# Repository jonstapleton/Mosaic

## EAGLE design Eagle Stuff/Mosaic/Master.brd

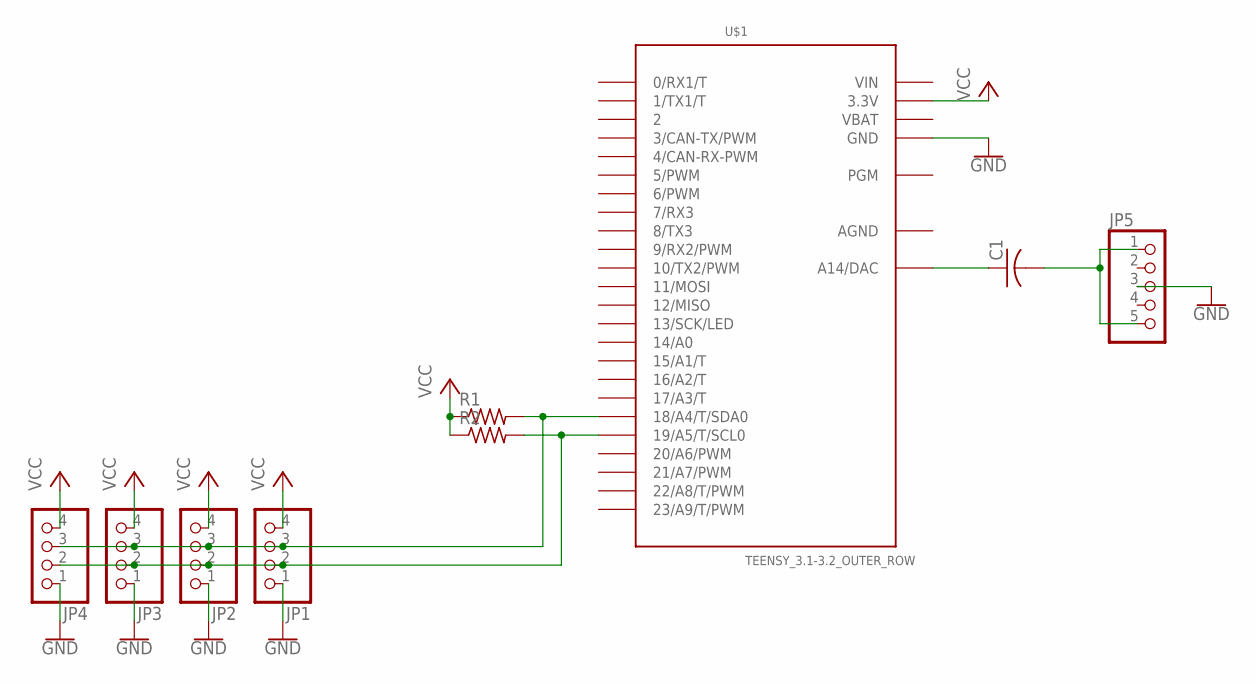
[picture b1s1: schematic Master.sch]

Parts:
C1: C-US025-030X050; C025-030X050
JP1, JP2, JP3, JP4: PINHD-1X4; 1X04
JP5: PINHD-1X5; 1X05
R1, R2: R-US_0207/7; 0207/7
U$1: TEENSY_3.1-3.2_OUTER_ROW; TEENSY_3.0-3.2&LC_OUTER_ROW

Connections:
AGND: U$1.AGND
GND: JP1.1, JP2.1, JP3.1, JP4.1, JP5.3, U$1.GND, U$1.GND1 (GND)
unnamed: JP1.3, JP2.3, JP3.3, JP4.3, R1.2, U$1.18/A4 (18/A4/T/SDA0)
unnamed: JP1.2, JP2.2, JP3.2, JP4.2, R2.2, U$1.19/A5 (19/A5/T/SCL0)
unnamed: C1.1, U$1.RESET/DAC (A14/DAC)
unnamed: C1.2, JP5.1, JP5.5
VBAT: U$1.VBAT
VCC: JP1.4, JP2.4, JP3.4, JP4.4, R1.1, R2.1, U$1.3.3V, U$1.3.3V1 (3.3V)
VIN: U$1.VIN

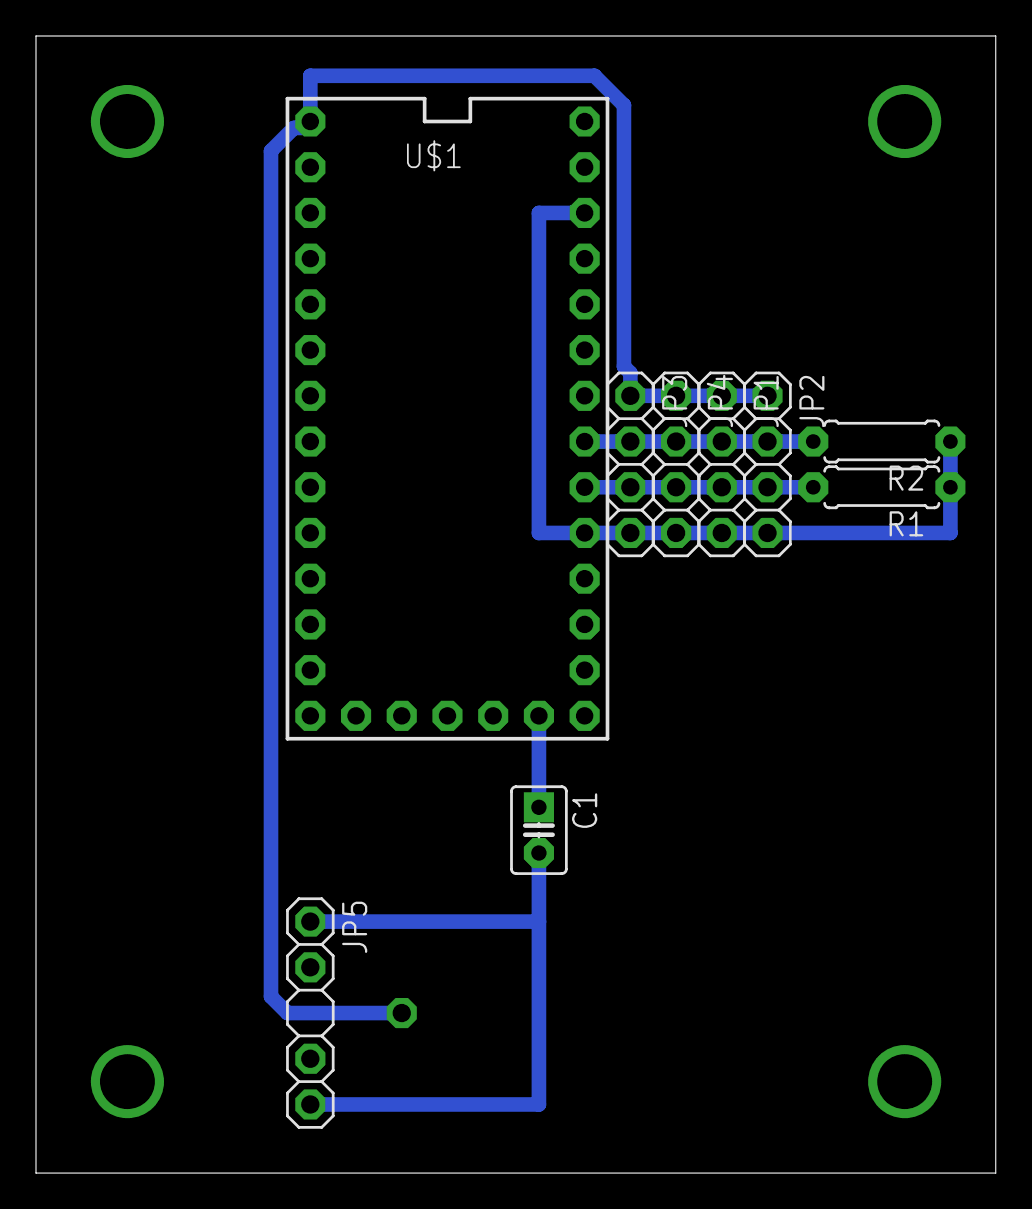
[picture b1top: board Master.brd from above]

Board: 2 copper layers, 53.3 x 63.2 mm, 9 parts (0 on the bottom side), 6 nets.

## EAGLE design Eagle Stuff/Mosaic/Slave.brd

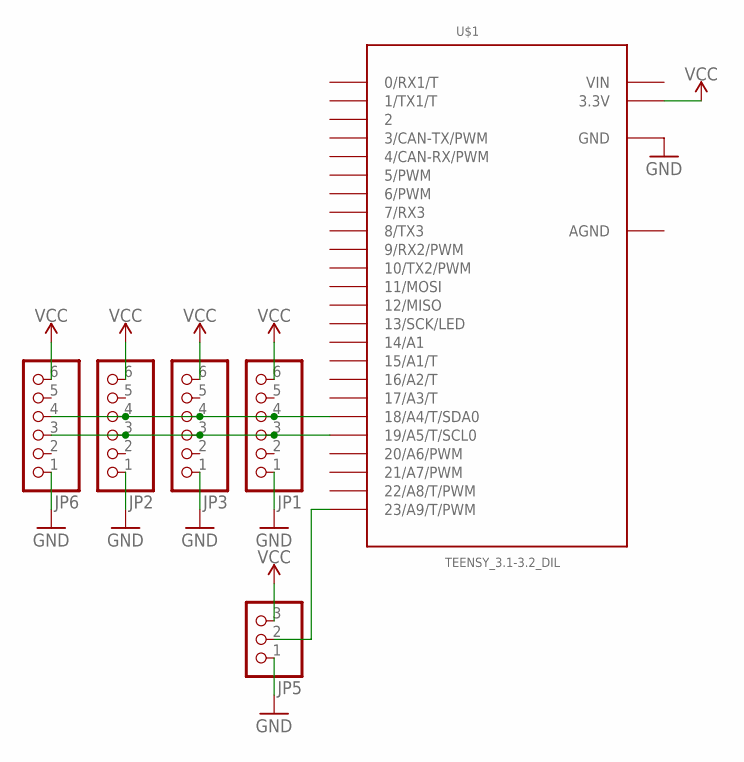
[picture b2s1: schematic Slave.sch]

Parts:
JP1: PINHD-1X6; 1X06
JP2, JP3, JP6: PINHD-1X6/90; 1X06/90
JP5: PINHD-1X3; 1X03
U$1: TEENSY_3.1-3.2_DIL; TEENSY_3.0-3.2&LC_DIL

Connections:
AGND: U$1.AGND
GND: JP1.1, JP2.1, JP3.1, JP5.1, JP6.1, U$1.GND
unnamed: JP5.2, U$1.23/A9 (23/A9/T/PWM)
unnamed: JP1.3, JP2.3, JP3.3, JP6.3, U$1.19/A5 (19/A5/T/SCL0)
unnamed: JP1.4, JP2.4, JP3.4, JP6.4, U$1.18/A4 (18/A4/T/SDA0)
VCC: JP1.6, JP2.6, JP3.6, JP5.3, JP6.6, U$1.3.3V
VIN: U$1.VIN

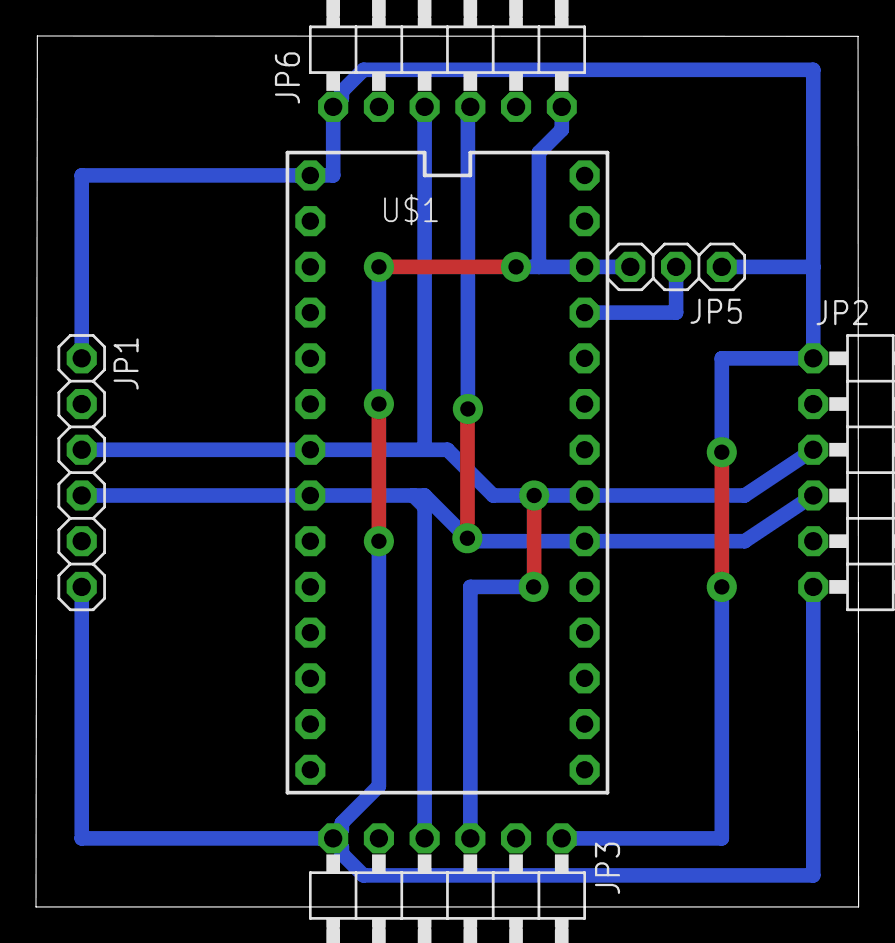
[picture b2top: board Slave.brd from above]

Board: 2 copper layers, 45.7 x 48.4 mm, 6 parts (0 on the bottom side), 5 nets.

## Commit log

2017-07-29 Initial File Upload
    I really hope this doesn't make me lose my stuff.
2017-07-29 Added knob tile
2017-07-29 Knob Tile
    I think this is the save that I have in the branch. No good, man.
2017-07-29 Organized into folders
2017-07-29 Added Mosaic 2.0 sketches
    The only one that works is the master module code
2017-07-29 Optimized for Mosaic 2.1
    Commented out color cycle code, added condition for MIDI or not once Audio is implemented.
2017-07-30 Tested Button Tile
    Trim fat later, only optimized for MIDI
2017-07-30 Increment addresses during upload
2017-07-30 Initial commit for knobtile
2017-07-31 Incremented all tiles through, all tested and functional
2017-07-31 Initial commit for master board
2017-07-31 Organized into Project
    I hope this doesn't make me lose my work.
2017-07-31 Added I2C Connector, moved Slave board to origin
2017-08-01 Ignore backup files
2017-08-01 Ignored Eagle backup files
2017-08-01 DRC Adjustments
2017-08-01 Finished Master enclosure
2017-08-01 Updated gitignore to avoid Eagle files
2017-08-01 Final edits before etching
2017-08-01 ignore SketchUp backup files
2017-08-01 Final edit before cutting
2017-08-01 Layout for cutting
2017-08-01 Fixed capacitor drill hole diameter
2017-08-01 gitignore
2017-08-01 Created spacer
2017-08-03 Ignore Eagle stuff
2017-08-03 Successful counter section
2017-08-03 Successful step invokation
2017-08-03 Test this!
2017-08-03 New master sketch
2017-08-10 These still don't work.

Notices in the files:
parts and their libraries:
SparkFun-PowerSymbols: Licensing: Creative Commons ShareAlike 4.0 International - https://creativecommons.org/licenses/by-sa/4.0
